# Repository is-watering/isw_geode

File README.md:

# ISW-GEODE

ISW-GEODE is a gaming macro pad designed primarily for playing Minecraft.

[Build guide](doc/buildguide.md)

## Dependencies (KiCad)
* [is-watering/isw-kbd-lib](https://github.com/is-watering/isw-kbd-lib)
* [Salicylic-acid3/KiCAD_FootPrint](https://github.com/Salicylic-acid3/KiCAD_FootPrint)
* [koktoh/BrownSugar_KBD_KiCad_Library](https://github.com/koktoh/BrownSugar_KBD_KiCad_Library)

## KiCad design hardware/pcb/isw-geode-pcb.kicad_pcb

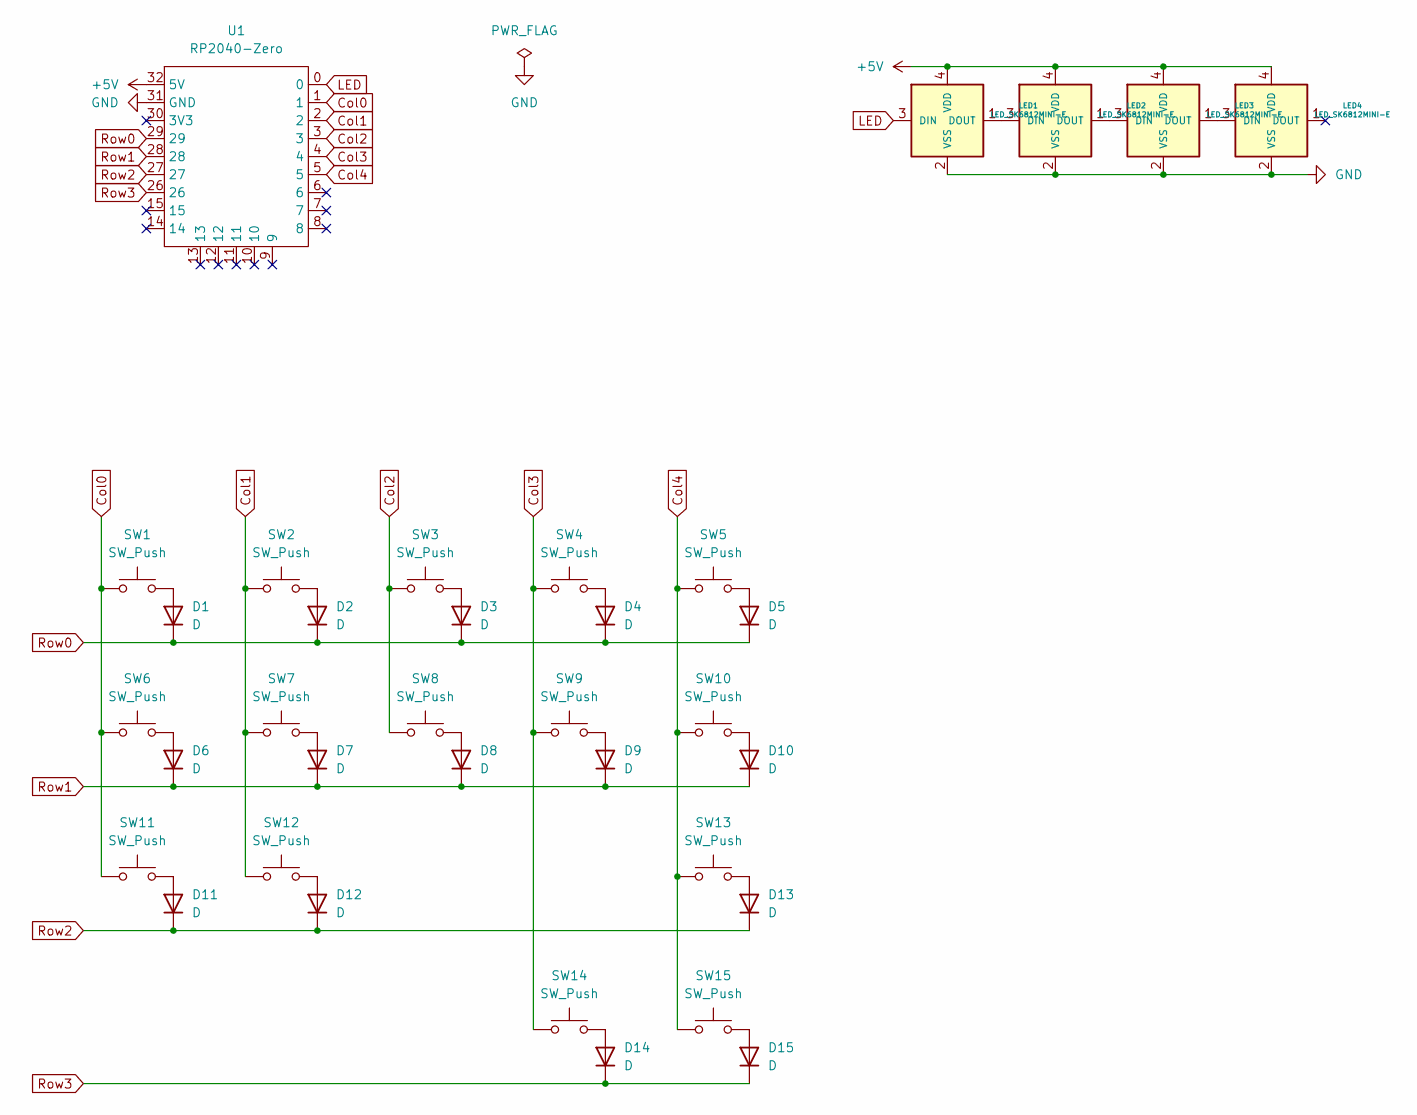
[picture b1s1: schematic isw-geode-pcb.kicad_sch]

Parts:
D1, D2, D3, D4, D5, D6, D7, D8, D9, D10, D11, D12, D13, D14, D15: D; Diode_TH_SMD
LED1, LED2, LED3, LED4: LED_SK6812MINI-E; LED_SK6812MINI-E_BL
SW1, SW2, SW3, SW4, SW5, SW6, SW7, SW8, SW9, SW10, SW11, SW12, SW13, SW14, SW15: SW_Push; CherryMX_Hotswap_1u
U1: RP2040-Zero; RP2040-Zero-THT

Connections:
+5V: LED1.4 (VDD), LED2.4 (VDD), LED3.4 (VDD), LED4.4 (VDD), U1.32 (5V)
Col0: SW1.1, SW6.1, SW11.1, U1.1
Col1: SW2.1, SW7.1, SW12.1, U1.2
Col2: SW3.1, SW8.1, U1.3
Col3: SW4.1, SW9.1, SW14.1, U1.4
Col4: SW5.1, SW10.1, SW13.1, SW15.1, U1.5
GND: LED1.2 (VSS), LED2.2 (VSS), LED3.2 (VSS), LED4.2 (VSS), U1.31 (GND)
LED: LED1.3 (DIN), U1.0
unnamed: D1.2 (A), SW1.2
unnamed: D2.2 (A), SW2.2
unnamed: D3.2 (A), SW3.2
unnamed: D4.2 (A), SW4.2
unnamed: D5.2 (A), SW5.2
unnamed: D6.2 (A), SW6.2
unnamed: D7.2 (A), SW7.2
unnamed: D8.2 (A), SW8.2
unnamed: D9.2 (A), SW9.2
unnamed: D10.2 (A), SW10.2
unnamed: D11.2 (A), SW11.2
unnamed: D12.2 (A), SW12.2
unnamed: D13.2 (A), SW13.2
unnamed: D14.2 (A), SW14.2
unnamed: D15.2 (A), SW15.2
unnamed: LED1.1 (DOUT), LED2.3 (DIN)
unnamed: LED2.1 (DOUT), LED3.3 (DIN)
unnamed: LED3.1 (DOUT), LED4.3 (DIN)
Row0: D1.1 (K), D2.1 (K), D3.1 (K), D4.1 (K), D5.1 (K), U1.29
Row1: D6.1 (K), D7.1 (K), D8.1 (K), D9.1 (K), D10.1 (K), U1.28
Row2: D11.1 (K), D12.1 (K), D13.1 (K), U1.27
Row3: D14.1 (K), D15.1 (K), U1.26

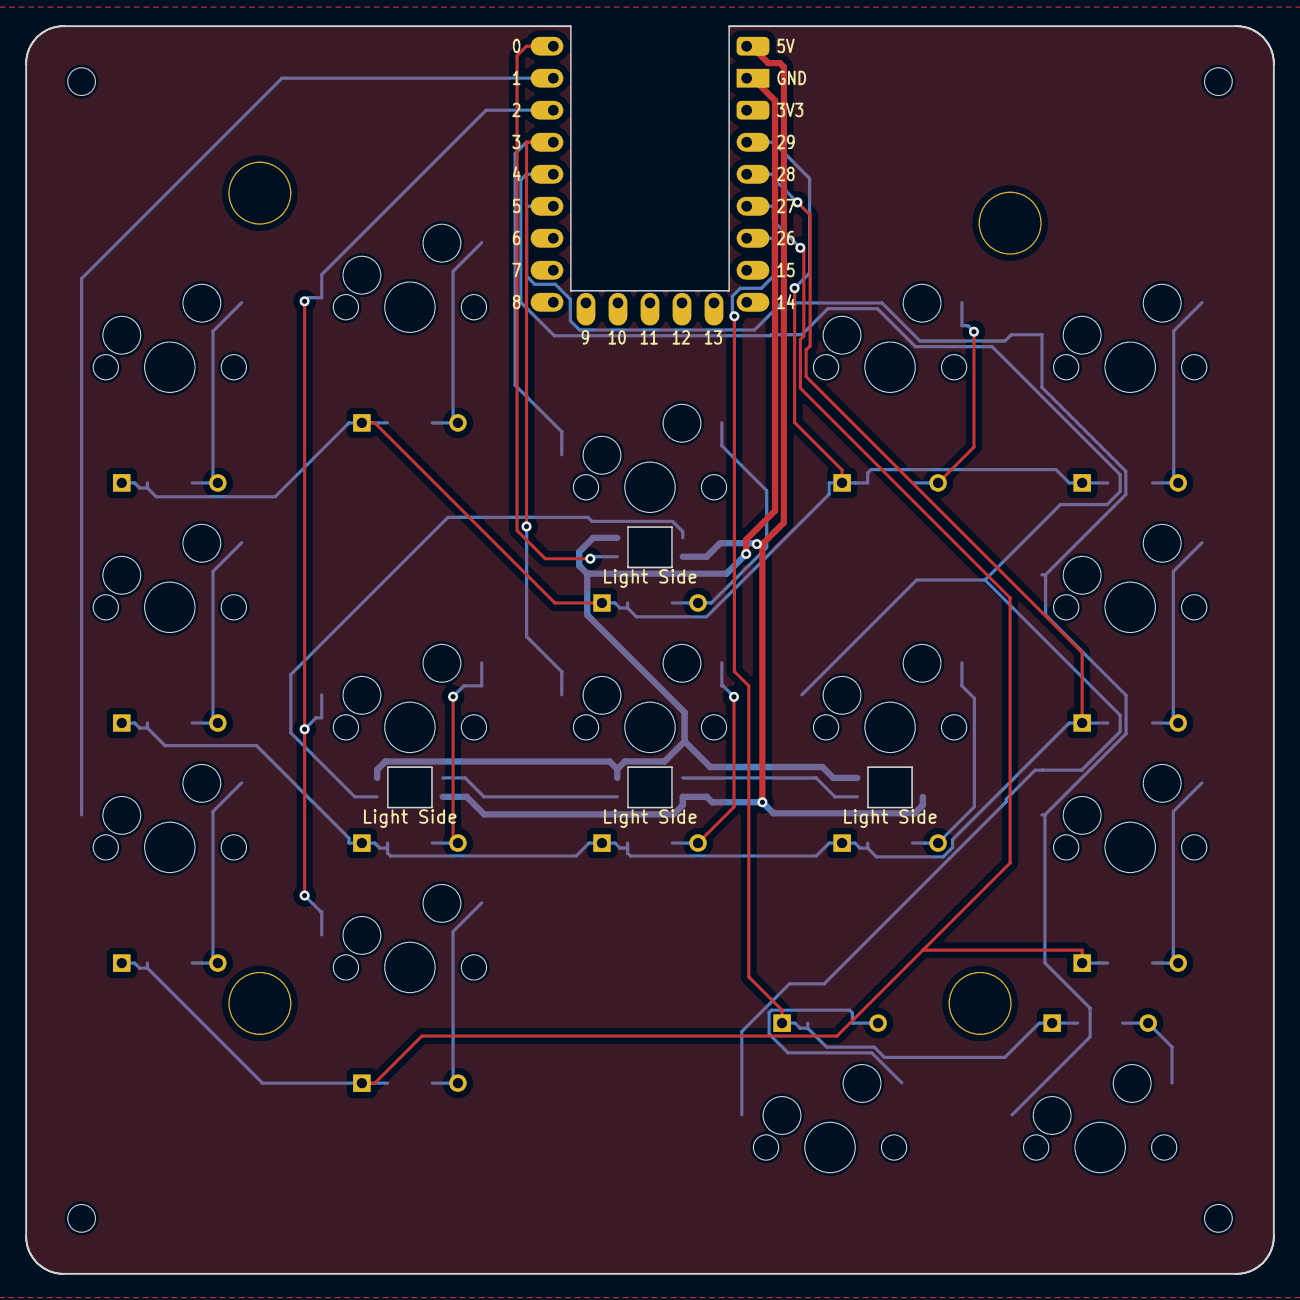
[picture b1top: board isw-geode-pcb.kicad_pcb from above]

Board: 2 copper layers, 99.0 x 99.0 mm, 43 parts (1 on the bottom side), 30 nets.

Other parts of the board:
Ref01, Ref02, Ref03, Ref04: Val01; m2_Spacer_Hole
Ref11, Ref12, Ref13, Ref14: Val02; m2_Screw_Hole
